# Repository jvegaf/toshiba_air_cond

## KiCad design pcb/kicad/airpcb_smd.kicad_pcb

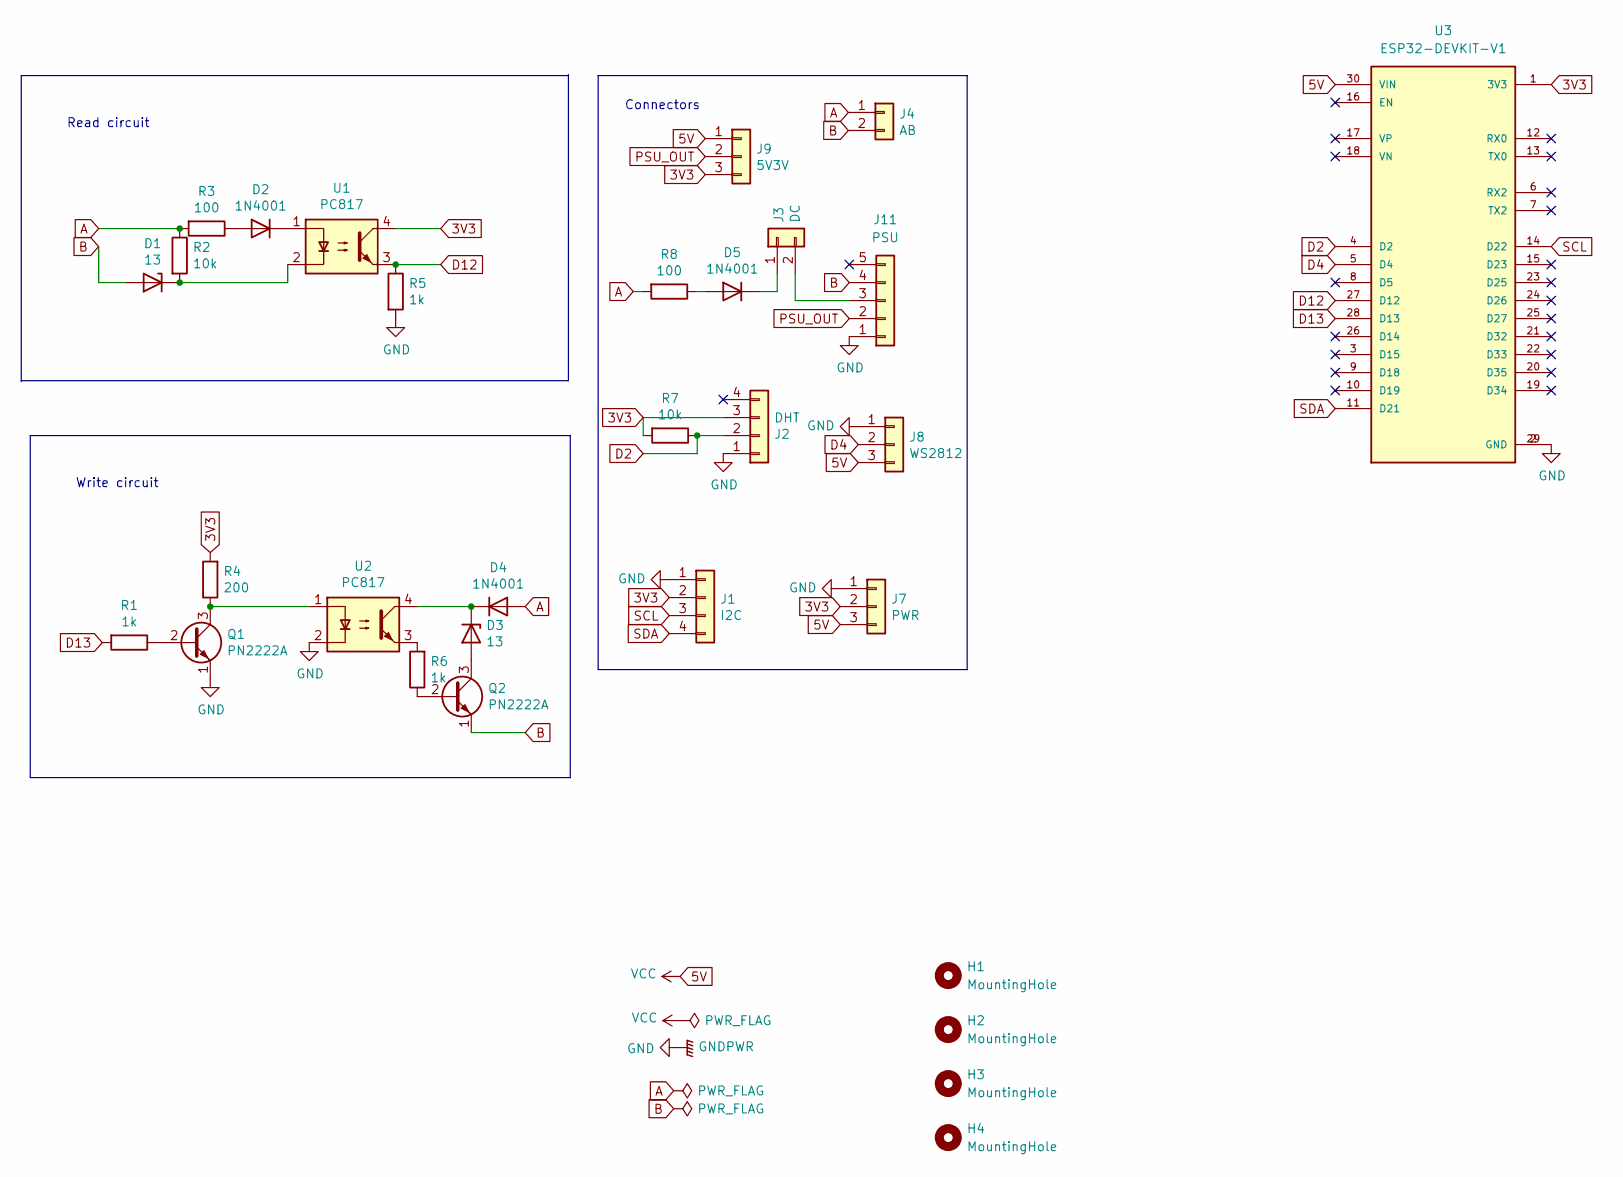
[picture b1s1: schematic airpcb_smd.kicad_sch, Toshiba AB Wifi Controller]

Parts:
D1, D3: 13; D_MiniMELF_Handsoldering
D2, D4, D5: 1N4001; D_SMA
H1, H2, H3, H4: MountingHole; MountingHole_2.2mm_M2_DIN965_Pad
J1: I2C; PinSocket_1x04_P2.54mm_Vertical
J2: DHT; PinSocket_1x04_P2.54mm_Vertical
J3: DC; PinSocket_1x02_P2.54mm_Vertical
J4: AB; TerminalBlock_Phoenix_MPT-0,5-2-2.54_1x02_P2.54mm_Horizontal
J7: PWR; PinSocket_1x03_P2.54mm_Vertical
J8: WS2812; PinSocket_1x03_P2.54mm_Vertical
J9: 5V3V; PinSocket_1x03_P2.54mm_Vertical
J11: PSU; PinSocket_1x05_P2.54mm_Vertical
Q1, Q2: PN2222A; TSOT-23_HandSoldering
R1, R5, R6: 1k; R_0805_2012Metric
R2, R7: 10k; R_0805_2012Metric
R3, R8: 100; R_0805_2012Metric
R4: 200; R_0805_2012Metric
U1, U2: PC817; DIP-4_W7.62mm
U3: ESP32-DEVKIT-V1; MODULE_ESP32_DEVKIT_V1; PARTREV N/A

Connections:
3V3: J1.2, J2.3, J7.2, J9.3, R4.2, R7.2, U1.4, U3.1 (3V3)
5V: J7.3, J8.3, J9.1, U3.30 (VIN)
A: D4.2 (A), J4.1, R2.1, R3.2, R8.2
B: D1.2 (A), J4.2, J11.4, Q2.1 (E)
D2: J2.2, R7.1, U3.4 (D2)
D4: J8.2, U3.5 (D4)
D12: R5.1, U1.3, U3.27 (D12)
D13: R1.2, U3.28 (D13)
GND: J1.1, J2.1, J7.1, J8.1, J11.1, Q1.1 (E), R5.2, U2.2, U3.2 (GND), U3.29 (GND)
unnamed: D1.1 (K), R2.2, U1.2
unnamed: D2.1 (K), U1.1
unnamed: D2.2 (A), R3.1
unnamed: D3.1 (K), D4.1 (K), U2.4
unnamed: D3.2 (A), Q2.3 (C)
unnamed: D5.1 (K), J3.1
unnamed: D5.2 (A), R8.1
unnamed: J3.2, J11.3
unnamed: Q1.2 (B), R1.1
unnamed: Q1.3 (C), R4.1, U2.1
unnamed: Q2.2 (B), R6.1
unnamed: R6.2, U2.3
PSU_OUT: J9.2, J11.2
SCL: J1.3, U3.14 (D22)
SDA: J1.4, U3.11 (D21)

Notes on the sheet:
Connectors
Write circuit
Read circuit

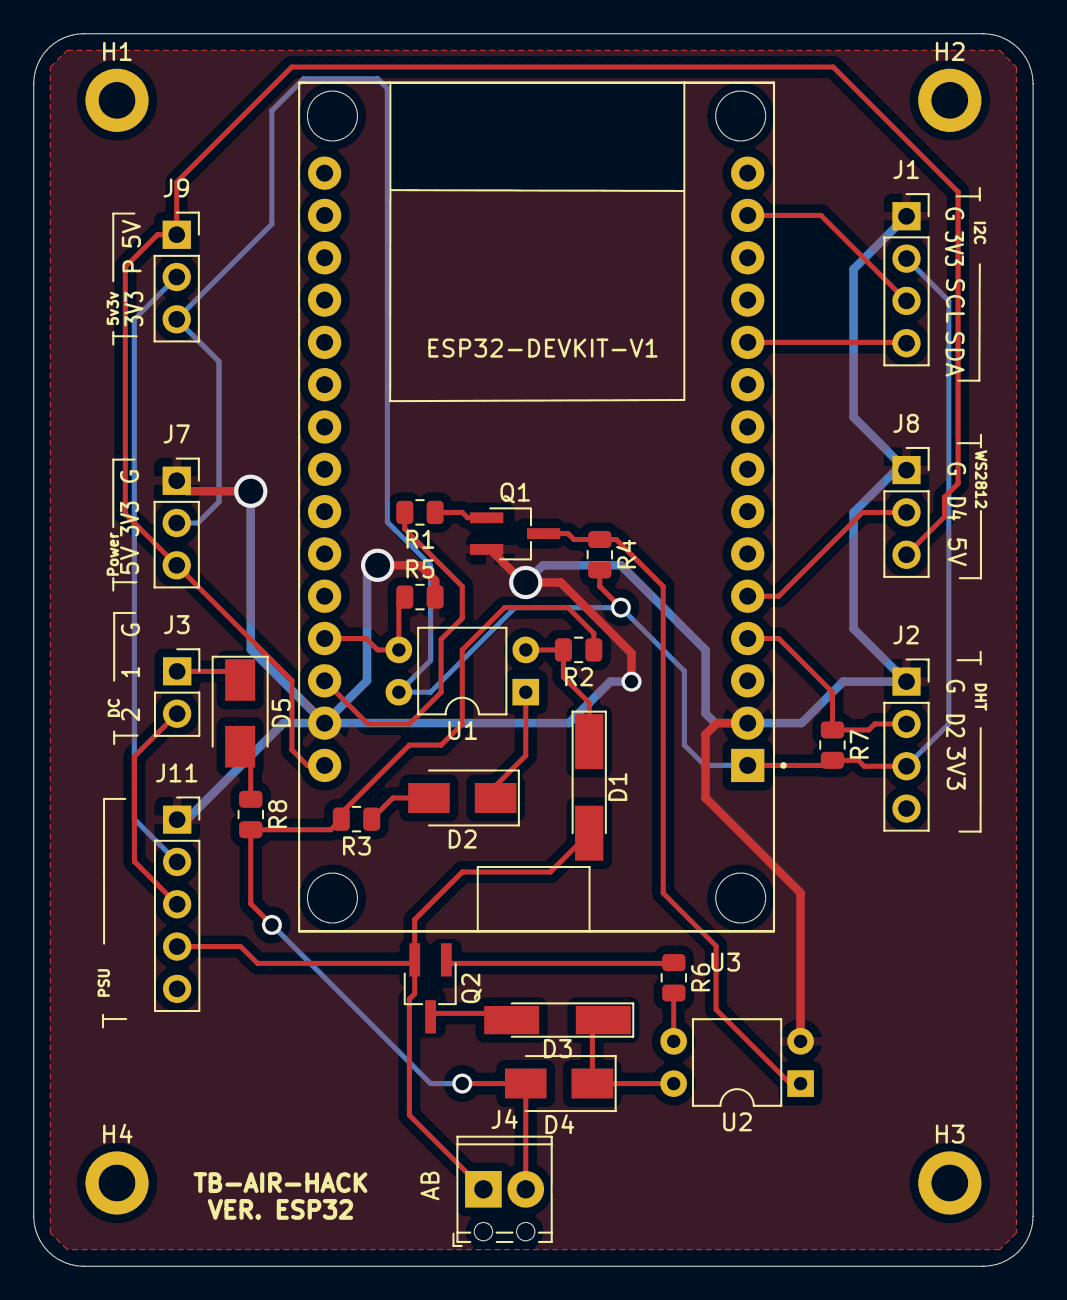
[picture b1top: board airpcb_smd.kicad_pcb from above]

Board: 2 copper layers, 60.0 x 74.0 mm, 30 parts (0 on the bottom side), 24 nets.

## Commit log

2022-03-27 added gitignore
2022-03-27 feat(pcb kicad project): update to v6 * migrated to kicad v6
    * added nodemcu symbols & footprints ( nodemcu project lib )
2022-03-31 routing
2022-04-06 temporal hack for make a other refactoring
2022-04-06 remove unused vars
2022-04-06 join definitions
2022-04-07 extract to global const
2022-04-07 libs updates
2022-04-07 fix all compiler warnings
2022-04-08 hotfix include
2022-04-08 placing again includes
2022-04-08 rollback defines
2022-04-08 placed in one side
2022-04-08 littlefs hack fixed
2022-04-08 temp
2022-04-09 fail
2022-08-21 added esp32 in schematic
2022-08-25 schematic done
2022-08-25 pcb wip
2022-08-26 pcb done
2022-09-04 little refactor
2022-09-26 first changes
